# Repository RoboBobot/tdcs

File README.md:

# An LT3092 based tDCS driver

# WARNING: Currently un-tested.

## Main Features

* Adjustable current from 0.7mA to 2.1mA. 
* Adjustable voltage from 9V to 18V. Also banana jacks to accept other voltages.
* Clearly labeled Anode and Cathode banana jacks.
* Mostly through-hole parts, for easier assembly

## Tasteful PCB Artwork

!

!

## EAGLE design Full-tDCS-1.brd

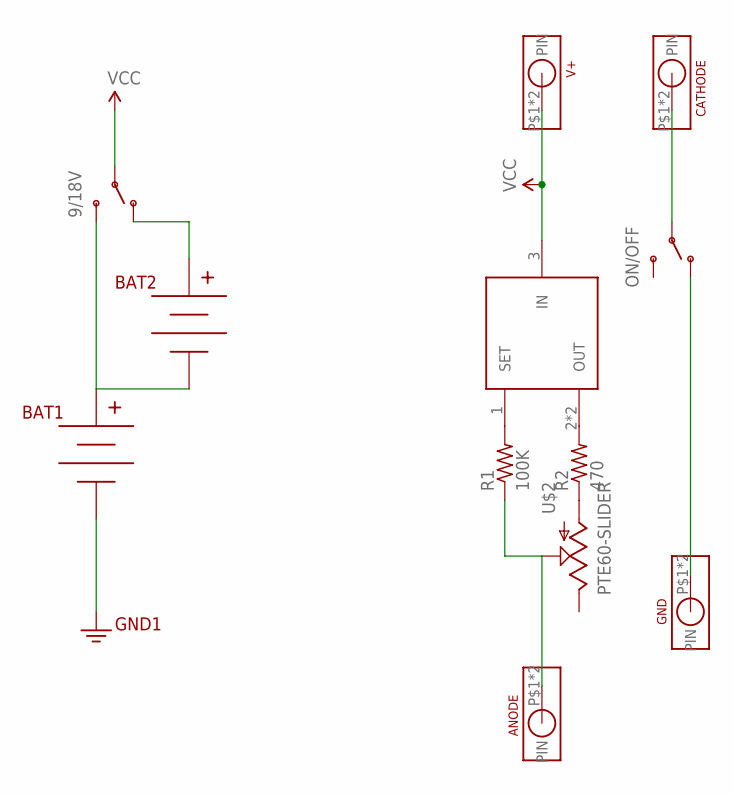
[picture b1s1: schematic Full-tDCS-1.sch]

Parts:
9/18V: SWITCH-SPDTPTH; SWITCH-SPDT
ANODE: BANANA-JACK; 105-0753-001-BANANA-JACK
BAT1, BAT2: BC9VPC
CATHODE: BANANA-JACK; 105-0753-001-BANANA-JACK
GND: BANANA-JACK; 105-0753-001-BANANA-JACK
ON/OFF: SWITCH-SPDTPTH; SWITCH-SPDT
R1: 100K; 0204/7
R2: 470; 0204/7
U$1: LT3092; SOT223
U$2: PTE60-SLIDER; SLIDER
V+: BANANA-JACK; 105-0753-001-BANANA-JACK

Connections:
GND: BAT1.V-, GND.P$1, GND.P$2, ON/OFF.1 (O)
unnamed: R1.2, U$1.1 (SET)
unnamed: R2.2, U$1.2 (OUT), U$1.4 (OUT)
unnamed: R2.1, U$2.1 (A)
unnamed: 9/18V.3 (S), BAT1.V+, BAT2.V-
unnamed: 9/18V.1 (O), BAT2.V+
unnamed: CATHODE.P$1, CATHODE.P$2, ON/OFF.2
unnamed: ANODE.P$1, ANODE.P$2, R1.1, U$2.2 (S)
VCC: 9/18V.2, U$1.3 (IN), V+.P$1, V+.P$2

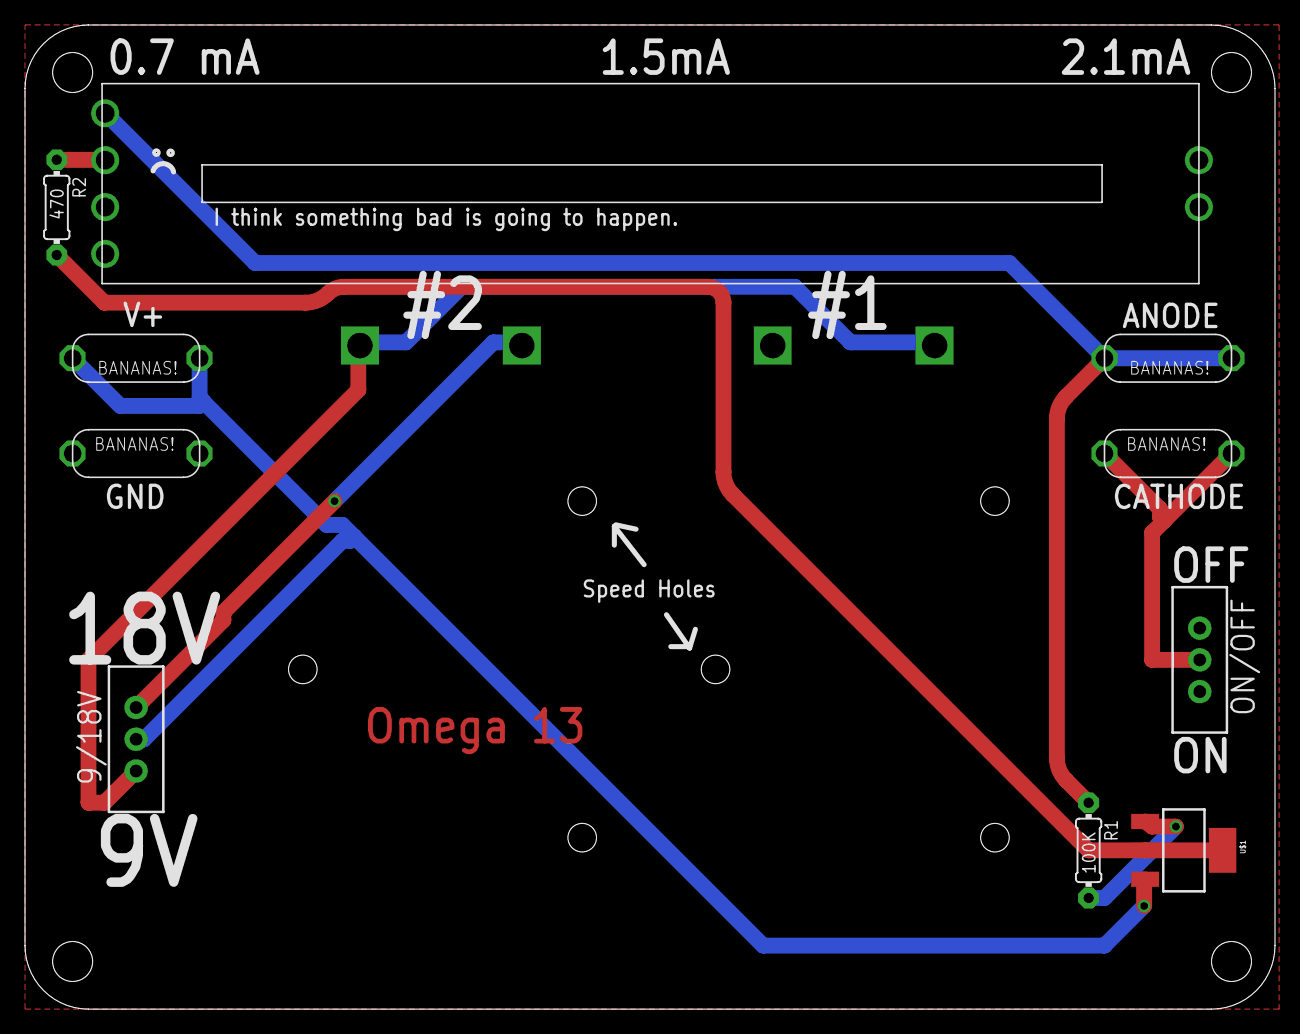
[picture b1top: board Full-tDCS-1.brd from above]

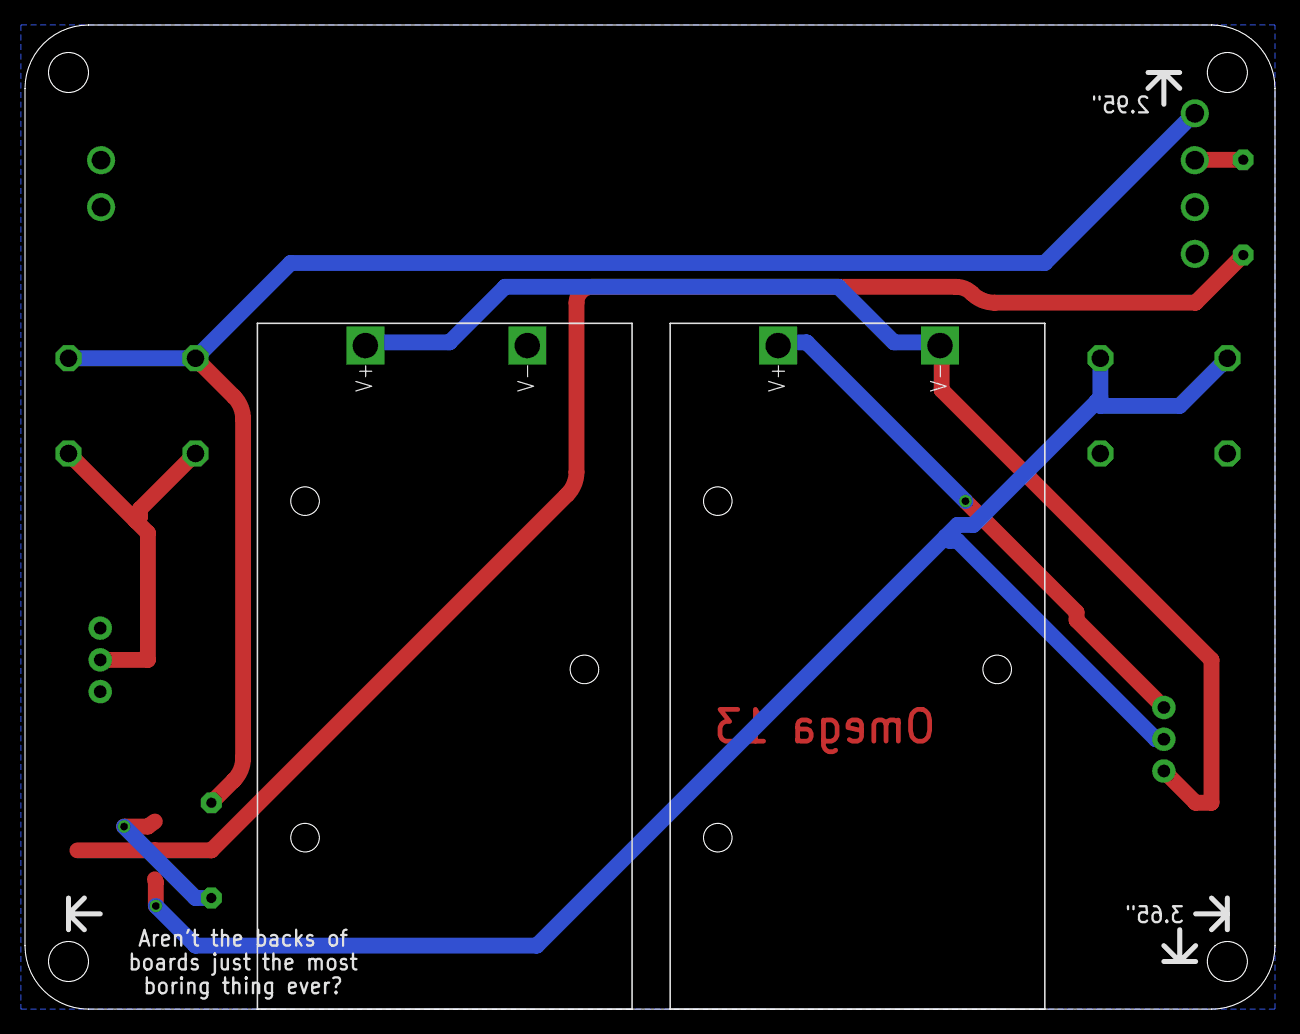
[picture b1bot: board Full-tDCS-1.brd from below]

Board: 2 copper layers, 100.0 x 78.7 mm, 12 parts (2 on the bottom side), 9 nets.

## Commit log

2014-08-22 First commit.
2014-08-22 BRD and SCH
2014-08-22 Digikey BOM.
2014-08-22 PCB artwork.
2014-08-22 Added warning.

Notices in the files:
parts and their libraries:
SparkFun-Connectors: Licensing: Creative Commons ShareAlike 4.0 International - https://creativecommons.org/licenses/by-sa/4.0
